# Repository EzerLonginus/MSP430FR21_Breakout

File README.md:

# MSP430FR21_Breakout
Basic breakout for the MSP430FR2111 chip

## Description

This board is a simple breakout using the [MSP430FR2111](www.ti.com/lit/ds/symlink/msp430fr2111.pdf) chip.  All the pins of the chip are broken out into separate headers.  There is an additional header on the top of the board to allow for plugging directly into the MSP-EXP430FR2311 evaluation board to upload code.  The breakout can accept 5V through the onboard regulator, or 3.3V directly.  There is a reset and onboard power indication LED. There is also a slot for a 32.768kHz clock and onboard LED connected directly to P2.0, for testing.  

### Front

### Back

## Purpose
I was looking to try out some development on the MSP430 series, slightly beyond the launch pads, and found a fairly [inexpensive chip](https://www.lcsc.com/product-detail/Microcontrollers-MCU-MPU-SOC_Texas-Instruments-MSP430FR2111IPW16_C1340043.html) to try to develop for.
I did make a slight error on the board that was ordered, which called out for 100nF capacitor on the reset line.  This actually needs to be 1nF, and has been fixed in the susequent gerber and design files.  Otherwise, the board basic goal has been achieved, and I'll continue to play around with the TI chip and architecture in the coming months to see what that is like.

## Schematic

## Layout

## Updates & Fixes
### Version 1
* Continue testing functionality of board and breakout
* Add some test code for the breakout
* Updated Reset capacitor or 1nF

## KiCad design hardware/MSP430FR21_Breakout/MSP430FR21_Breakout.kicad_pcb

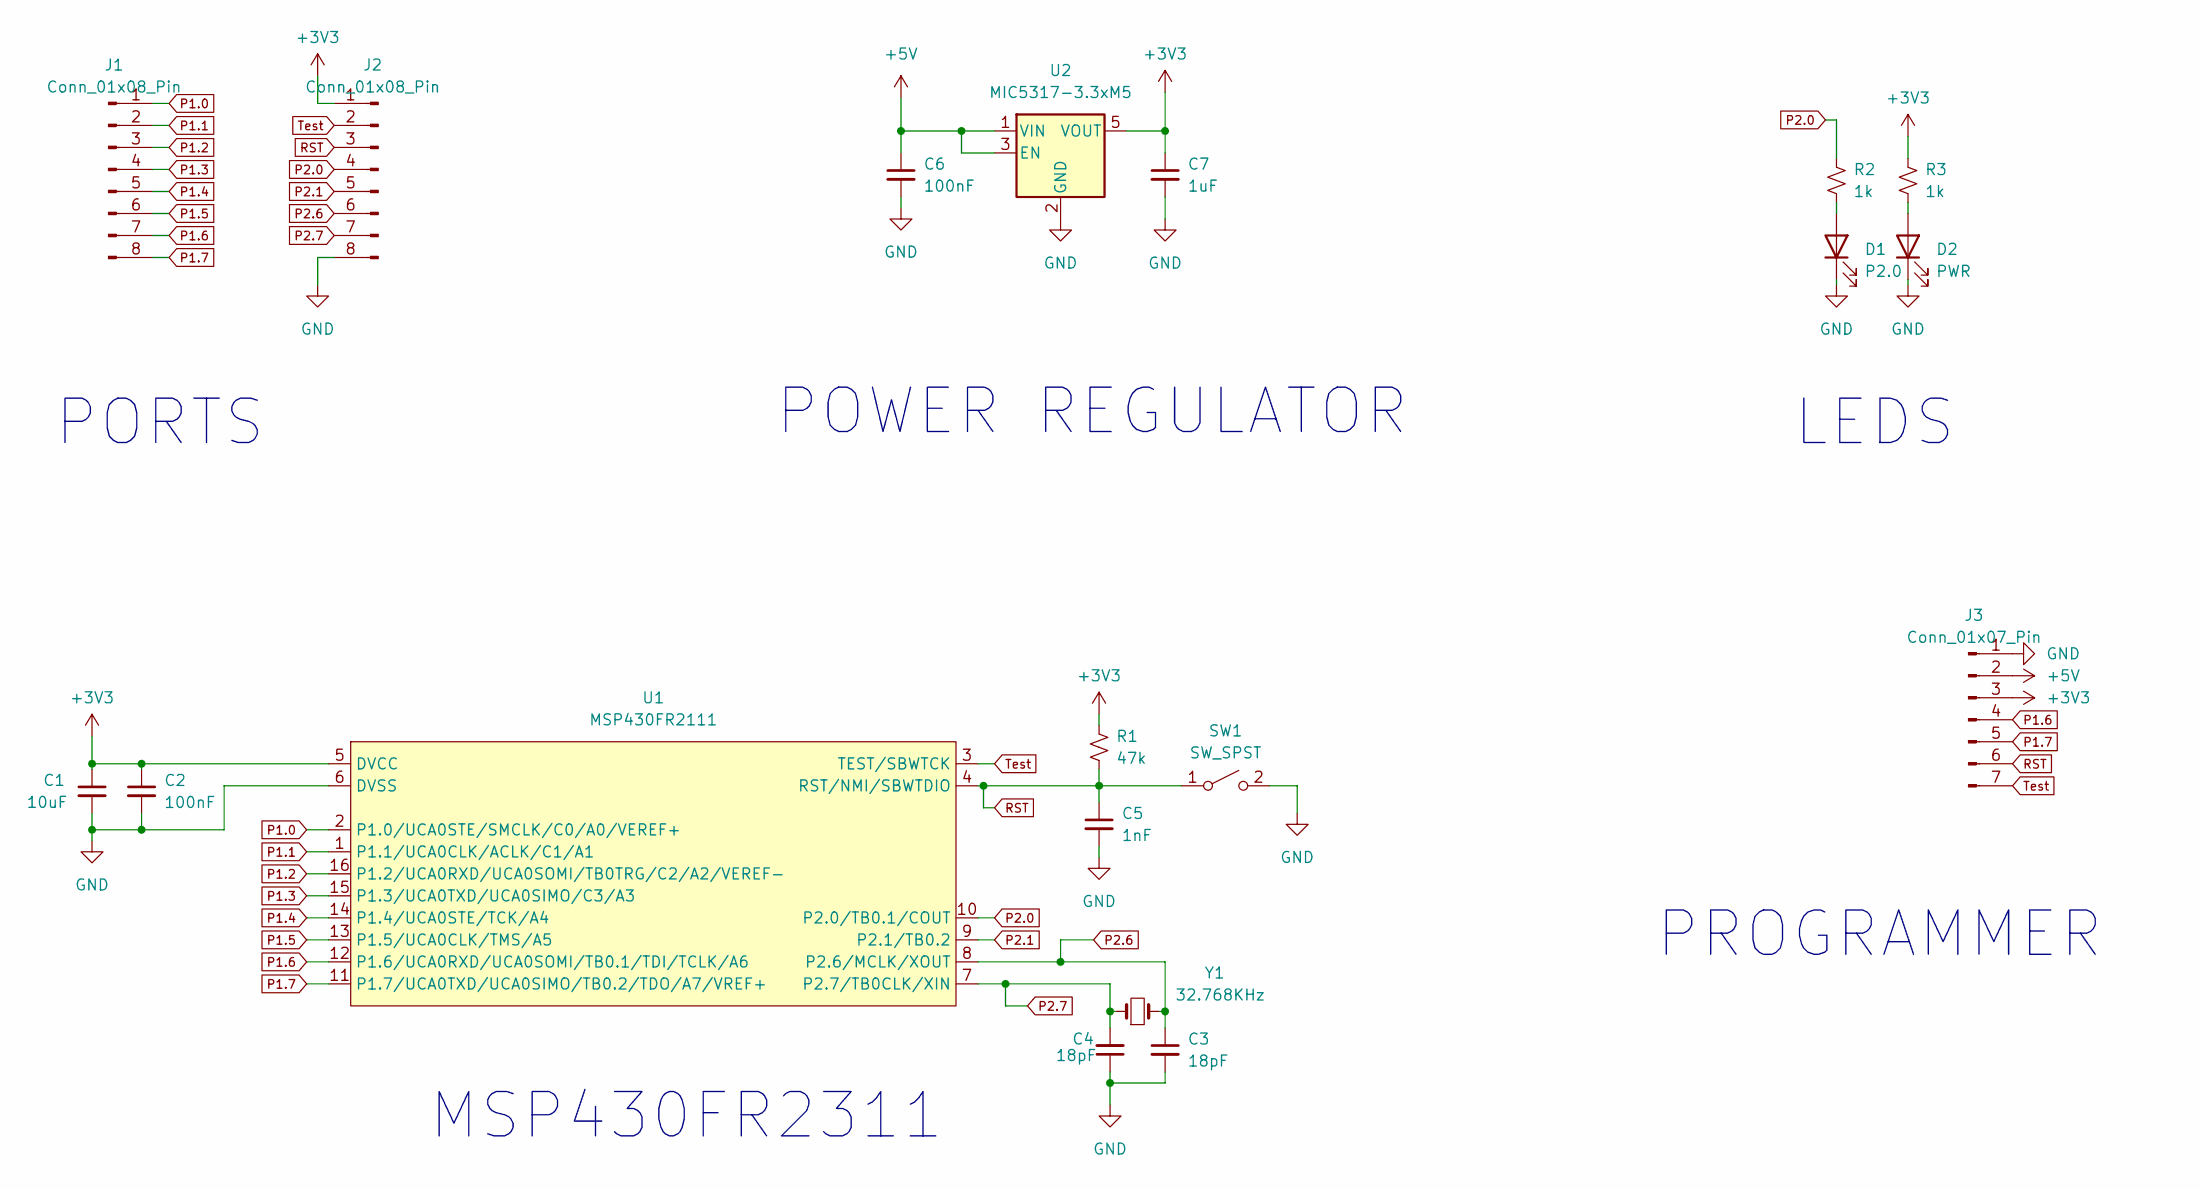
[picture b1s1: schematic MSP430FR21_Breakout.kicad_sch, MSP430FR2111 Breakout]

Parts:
C1: 10uF; C_0805_2012Metric
C2, C6: 100nF; C_0603_1608Metric
C3, C4: 18pF; C_0603_1608Metric
C5: 1nF; C_0603_1608Metric
C7: 1uF; C_0603_1608Metric
D1: P2.0; LED_0603_1608Metric_Pad1.05x0.95mm_HandSolder
D2: PWR; LED_0603_1608Metric_Pad1.05x0.95mm_HandSolder
J1, J2: Conn_01x08_Pin; PinHeader_1x08_P2.54mm_Vertical
J3: Conn_01x07_Pin; PinHeader_1x07_P2.54mm_Vertical
R1: 47k; R_0603_1608Metric_Pad0.98x0.95mm_HandSolder
R2, R3: 1k; R_0603_1608Metric_Pad0.98x0.95mm_HandSolder
SW1: SW_SPST; SW_PUSH_6mm
U1: MSP430FR2111; TSSOP-16_4.4x5mm_P0.65mm
U2: MIC5317-3.3xM5; SOT-23-5
Y1: 32.768KHz; Crystal_SMD_EuroQuartz_EQ161-2Pin_3.2x1.5mm_HandSoldering

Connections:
+3V3: C1.1, C2.1, C7.1, J2.1, J3.3, R1.1, R3.1, U1.5 (DVCC), U2.5 (VOUT)
+5V: C6.1, J3.2, U2.1 (VIN), U2.3 (EN)
GND: C1.2, C2.2, C3.2, C4.1, C5.2, C6.2, C7.2, D1.1 (K), D2.1 (K), J2.8, J3.1, SW1.2 (B), U1.6 (DVSS), U2.2 (GND)
unnamed: D1.2 (A), R2.2
unnamed: D2.2 (A), R3.2
P1.0: J1.1, U1.2 (P1.0/UCA0STE/SMCLK/C0/A0/VEREF+)
P1.1: J1.2, U1.1 (P1.1/UCA0CLK/ACLK/C1/A1)
P1.2: J1.3, U1.16 (P1.2/UCA0RXD/UCA0SOMI/TB0TRG/C2/A2/VERE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)
P1.3: J1.4, U1.15 (P1.3/UCA0TXD/UCA0SIMO/C3/A3)
P1.4: J1.5, U1.14 (P1.4/UCA0STE/TCK/A4)
P1.5: J1.6, U1.13 (P1.5/UCA0CLK/TMS/A5)
P1.6: J1.7, J3.4, U1.12 (P1.6/UCA0RXD/UCA0SOMI/TB0.1/TDI/TCLK/A6)
P1.7: J1.8, J3.5, U1.11 (P1.7/UCA0TXD/UCA0SIMO/TB0.2/TDO/A7/VREF+)
P2.0: J2.4, R2.1, U1.10 (P2.0/TB0.1/COUT)
P2.1: J2.5, U1.9 (P2.1/TB0.2)
P2.6: C3.1, J2.6, U1.8 (P2.6/MCLK/XOUT), Y1.2
P2.7: C4.2, J2.7, U1.7 (P2.7/TB0CLK/XIN), Y1.1
RST: C5.1, J2.3, J3.6, R1.2, SW1.1 (A), U1.4 (RST/NMI/SBWTDIO)
Test: J2.2, J3.7, U1.3 (TEST/SBWTCK)

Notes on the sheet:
LEDS
POWER REGULATOR
PROGRAMMER
PORTS
MSP430FR2311

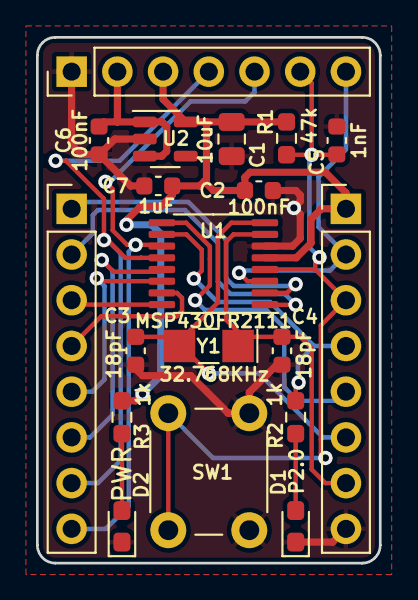
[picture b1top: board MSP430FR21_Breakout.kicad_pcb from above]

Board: 2 copper layers, 19.1 x 29.2 mm, 19 parts (0 on the bottom side), 19 nets.

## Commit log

2024-07-16 Updated Readme with Pictures
2024-07-16 Readme format change

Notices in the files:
README.md:
https://img.shields.io/badge/GPL-3.0-brightgreen
